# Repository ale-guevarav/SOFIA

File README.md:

# SOFIA - Sistema de Detección de Posturas

Sistema de visión por computadora desarrollado para el robot **SOFIA**, enfocado en la detección de la estructura corporal, manos y posturas de una persona en tiempo real.

El objetivo del proyecto es permitir que SOFIA pueda interpretar gestos corporales para interactuar con una persona durante una dinámica basada en el juego **Vaqueritos**.

## Primera entrega

En esta primera etapa se implementó el sistema base de visión por computadora. El programa utiliza una cámara para detectar a una persona y representar en tiempo real los puntos clave de su cuerpo y manos.

Actualmente el sistema permite:

* Capturar video en tiempo real mediante una cámara.
* Detectar la estructura corporal de una persona.
* Obtener los 33 landmarks proporcionados por MediaPipe Pose Landmarker.
* Dibujar los puntos y conexiones del esqueleto corporal.
* Filtrar landmarks corporales con baja visibilidad.
* Detectar hasta dos manos simultáneamente.
* Obtener 21 landmarks por cada mano.
* Dibujar las articulaciones y conexiones de los dedos.
* Procesar Pose y Hands simultáneamente.
* Mostrar los FPS durante la ejecución.
* Indicar visualmente si existe una persona detectada.
* Registrar métricas de desempeño (tasa de acierto, tiempo de respuesta y FPS promedio) y generar reportes en Excel y Markdown.

El sistema puede trabajar con hasta **75 landmarks simultáneamente**:

```text
33 landmarks del cuerpo
+ 21 landmarks de la mano izquierda
+ 21 landmarks de la mano derecha
= 75 landmarks
```

---

## Tecnologías utilizadas

### Python 3.12

Se eligió Python debido a su facilidad de desarrollo y a la gran cantidad de librerías disponibles para visión por computadora y procesamiento de datos.

También permite realizar prototipos rápidamente y cuenta con compatibilidad con las herramientas utilizadas en el proyecto.

### Visual Studio Code

Se utiliza Visual Studio Code como entorno de desarrollo debido a que es ligero, permite trabajar fácilmente con entornos virtuales de Python y cuenta con herramientas de depuración, terminal integrada y soporte para Git.

### OpenCV

OpenCV se utiliza principalmente para:

* Acceder a la cámara.
* Capturar los frames de video.
* Convertir formatos de imagen.
* Dibujar líneas, puntos y texto sobre la imagen.
* Mostrar el resultado del procesamiento en tiempo real.

### MediaPipe

MediaPipe proporciona los modelos de visión utilizados para obtener los landmarks del cuerpo y las manos sin necesidad de entrenar un modelo propio.

Se utilizan dos componentes:

**Pose Landmarker**

* Detecta la estructura corporal.
* Proporciona 33 landmarks.
* Permite conocer la posición de hombros, brazos, codos, muñecas, torso, piernas y otros puntos del cuerpo.

**Hand Landmarker**

* Detecta hasta dos manos.
* Proporciona 21 landmarks por mano.
* Permite obtener información de las articulaciones de los dedos.

El uso de Hand Landmarker será especialmente útil para reconocer gestos donde la posición de los dedos sea importante.

### NumPy

NumPy forma parte de las herramientas utilizadas para el procesamiento numérico y será utilizado para operaciones geométricas relacionadas con los landmarks, como cálculo de distancias, vectores y ángulos entre articulaciones.

### Matplotlib y openpyxl

Se utilizan para generar los reportes de métricas:

* **Matplotlib** crea las gráficas en imagen (pastel, barras, líneas y matriz de confusión) para el reporte en Markdown.
* **openpyxl** crea el archivo de Excel con tablas y gráficas nativas que se pueden editar.

---

## ¿Por qué se eligieron estas tecnologías?

La combinación de **Python + OpenCV + MediaPipe** permite desarrollar un sistema de visión por computadora en tiempo real sin necesidad de crear y entrenar desde cero una red neuronal para reconocimiento corporal.

Las principales ventajas para este proyecto son:

* Facilidad de implementación.
* Modelos previamente entrenados.
* Procesamiento en tiempo real.
* Detección corporal y de manos.
* Compatibilidad con cámaras convencionales.
* Gran cantidad de documentación y soporte.
* Posibilidad de calcular posturas mediante geometría a partir de los landmarks.
* Facilidad para integrar posteriormente el sistema con la lógica de SOFIA.

---

## Estructura del proyecto

```text
sofia_pose_detection/
│
├── models/
│   ├── pose_landmarker.task
│   └── hand_landmarker.task
│
├── metrics/                  (se crea automáticamente)
│   ├── sesion_*.json
│   └── reportes/
│
├── main.py
├── pose_detector.py
├── pose_connections.py
├── hand_detector.py
├── hand_connections.py
├── gesture_detector.py
├── geometry_utils.py
├── smoothing.py
├── metrics_logger.py
├── generate_report.py
├── requirements.txt
├── .gitignore
└── README.md
```

### `main.py`

Es el punto principal de ejecución del programa.

Se encarga de:

* Inicializar la cámara.
* Obtener los frames.
* Enviar las imágenes a los detectores.
* Coordinar Pose y Hands.
* Mostrar el resultado.
* Calcular los FPS.
* Registrar las métricas de desempeño.
* Liberar los recursos al finalizar.

### `pose_detector.py`

Contiene la lógica relacionada con MediaPipe Pose Landmarker.

Se encarga de detectar y dibujar la estructura corporal.

### `pose_connections.py`

Define las conexiones utilizadas para representar gráficamente el esqueleto corporal.

### `hand_detector.py`

Contiene la lógica relacionada con MediaPipe Hand Landmarker.

Se encarga de detectar y dibujar las manos y sus articulaciones.

### `hand_connections.py`

Define las conexiones entre los 21 landmarks de cada mano.

### `gesture_detector.py`

Contiene las reglas geométricas para reconocer los cinco gestos a partir de los landmarks.

### `geometry_utils.py`

Funciones de apoyo para calcular distancias, ángulos y distancias normalizadas.

### `smoothing.py`

Suavizado de landmarks (EMA) y confirmación temporal para evitar detecciones inestables.

### `metrics_logger.py`

Mide el desempeño del sistema mientras se ejecuta: FPS, latencia por frame y resultados de las pruebas. Guarda todo en un archivo JSON.

### `generate_report.py`

Lee el JSON de métricas y genera el reporte en Excel (`.xlsx`) y Markdown (`.md`) con tablas y gráficas.

### `models/`

Contiene los modelos utilizados por MediaPipe:

```text
pose_landmarker.task
hand_landmarker.task
```

---

# Posturas y gestos propuestos

Para la interacción con SOFIA se diseñaron cinco gestos inspirados en la dinámica del juego **Vaqueritos**.

En esta primera etapa los gestos se encuentran diseñados conceptualmente. Su reconocimiento automático será implementado en una etapa posterior utilizando los landmarks obtenidos por Pose Landmarker y Hand Landmarker.

## 1. INICIO - Tres palmadas

**Tipo:** Gesto dinámico.

La persona coloca las manos cerca de los muslos y realiza tres palmadas consecutivas sobre ellos.

**Función:**

Indicar el inicio de la partida o una transición hacia el modo de juego.

**Detección propuesta:**

Se analizará la distancia entre las muñecas/manos y la zona de los muslos a través de varios frames, utilizando un contador para reconocer tres movimientos consecutivos.

---

## 2. RECARGAR

**Tipo:** Postura estática.

La persona flexiona ambos brazos y coloca las manos aproximadamente a la altura de los hombros.

**Función:**

Recargar munición dentro del juego.

**Detección propuesta:**

Se utilizarán las posiciones de:

* Hombros.
* Codos.
* Muñecas.

A partir de estos landmarks será posible calcular ángulos y distancias para determinar si ambos brazos se encuentran en la posición esperada.

---

## 3. ESCUDO

**Tipo:** Postura estática.

La persona cruza los brazos frente al pecho.

**Función:**

Protegerse de un ataque.

**Detección propuesta:**

Se analizará la posición relativa de:

* Hombros.
* Codos.
* Muñecas.
* Torso.

Las muñecas deberán encontrarse cruzadas o posicionadas hacia lados opuestos del torso.

---

## 4. ATAQUE

**Tipo:** Postura principalmente estática.

La persona dirige los brazos hacia el frente y realiza con las manos un gesto similar a una pistola.

**Función:**

Realizar un ataque contra SOFIA.

**Detección propuesta:**

Pose Landmarker permitirá analizar la extensión y dirección de los brazos.

Hand Landmarker permitirá analizar individualmente los dedos para identificar una configuración similar a:

* Índice extendido.
* Pulgar extendido.
* Dedos medio, anular y meñique flexionados.

---

## 5. FIN / DESPEDIDA

**Tipo:** Gesto dinámico.

La persona levanta ambas manos y realiza un movimiento lateral de despedida.

**Función:**

Finalizar la interacción o indicar el término de la partida.

**Detección propuesta:**

Se analizará la posición de las manos durante varios frames para detectar cambios repetidos de dirección de izquierda a derecha.

---

# Flujo actual del sistema

```text
Cámara
   │
   ▼
OpenCV
   │
   ├───────────────┐
   ▼               ▼
Pose Landmarker   Hand Landmarker
   │               │
   ▼               ▼
33 landmarks      21 landmarks por mano
   │               │
   └───────┬───────┘
           ▼
Representación visual
           │
           ▼
Esqueleto + manos + FPS
```

---

# Flujo futuro

El sistema está diseñado para evolucionar hacia:

```text
Cámara
   │
   ▼
Pose + Hands
   │
   ▼
Landmarks
   │
   ▼
Detector de gestos
   │
   ├── INICIO
   ├── RECARGAR
   ├── ESCUDO
   ├── ATAQUE
   └── FIN
   │
   ▼
Lógica del juego
   │
   ▼
SOFIA
```

La lógica del juego podrá administrar aspectos como munición, acciones válidas, selección de acciones de SOFIA y condiciones de victoria o derrota.

---

# Instalación

## 1. Clonar el repositorio

```bash
git clone https://github.com/ale-guevarav/SOFIA
cd SOFIA
```

## 2. Crear un entorno virtual

```bash
python -m venv .venv
```

## 3. Activar el entorno virtual

En Windows PowerShell:

```powershell
.\.venv\Scripts\Activate.ps1
```

## 4. Instalar dependencias

```bash
pip install -r requirements.txt
```

> `requirements.txt` debe incluir `openpyxl` para poder generar el reporte en Excel.

---

# Ejecución

Con el entorno virtual activado:

```bash
python main.py
```

Se abrirá una ventana con la imagen de la cámara y la detección en tiempo real.

Para cerrar el programa:

```text
Presionar Q
```

Al cerrar se guardan automáticamente las métricas de la sesión y se genera el reporte (ver la siguiente sección).

---

# Pruebas y métricas de desempeño

El sistema incluye un modo de pruebas para medir qué tan bien funciona. Las métricas registradas son:

* **Tasa de acierto:** porcentaje de pruebas en las que el sistema reconoció el gesto correcto.
* **Tiempo de respuesta:** cuánto tarda el sistema en reconocer un gesto.
* **FPS promedio:** qué tan fluido corre el sistema.

## Controles

Las teclas solo funcionan si la **ventana de la cámara está seleccionada** (haz clic en ella antes de presionar).

| Tecla | Acción |
| --- | --- |
| `1` | Probar **INICIO** |
| `2` | Probar **RECARGAR** |
| `3` | Probar **ESCUDO** |
| `4` | Probar **ATAQUE** |
| `5` | Probar **FIN** |
| `0` / `x` | **Modo libre:** cancela la prueba actual, no registra nada y no muestra nada en pantalla |
| `s` | Guardar las métricas sin cerrar el programa |
| `q` | Salir, guardar las métricas y generar el reporte |

## ¿Cómo funciona una prueba?

Cada prueba pasa por cuatro fases:

```text
Presionar 1-5
     │
     ▼
TESTING: <gesto>  3 → 2 → 1        (naranja)
Preparación. Lo que se detecte aquí NO cuenta.
     │
     ▼
TESTING: <gesto>  YA!              (rojo parpadeando)
La persona hace el gesto. Tiene 6 segundos.
Aquí empieza a medirse el tiempo de respuesta.
     │
     ▼
ACIERTO (verde)  /  FALLO (rojo)
Se muestra 1.5 segundos.
     │
     ▼
Modo libre (pantalla limpia)
```

Mientras no se inicie una prueba, el sistema sigue midiendo FPS y latencia en segundo plano, pero no calcula la tasa de acierto, porque no sabe qué gesto se esperaba.

## ¿Cómo se califica una prueba?

El **primer gesto** que detecte el sistema después del "YA!" decide el resultado:

| Resultado | Qué significa |
| --- | --- |
| ✅ **Acierto** | El sistema detectó el gesto que se estaba probando. |
| ❌ **No detectado** | Pasaron los 6 segundos y el sistema no detectó nada. |
| ❌ **Confundido** | El sistema detectó un gesto diferente al que se estaba probando. |

Un gesto se cuenta solo en el momento en que **aparece** (cuando cambia la postura mostrada en pantalla). Si la persona mantiene un gesto por varios segundos, se cuenta como una sola detección.

## Reglas para hacer pruebas válidas

1. **Empezar en posición neutral**, con los brazos abajo. Si el gesto ya está hecho antes del "YA!", el sistema no ve un cambio y la prueba puede salir como *No detectado*.
2. **Esperar el "YA!"** antes de hacer el gesto. Lo que ocurre durante la cuenta regresiva no se toma en cuenta.
3. **Hacer un solo gesto por prueba.** Si se hace otro gesto primero, la prueba cuenta como *Confundido*.
4. **No iniciar otra prueba** mientras aparezca "TESTING". Hay que esperar a que termine o cancelarla con `0`.
5. **Mantener a la persona completa en cámara**, al menos de la cadera hacia arriba y con buena iluminación.
6. **Dividir los roles:** lo ideal es que una persona presione las teclas y otra haga los gestos.

## Protocolo recomendado

Para que los resultados sean representativos:

* Realizar **al menos 10 pruebas por gesto** (50 en total).
* Alternar el orden de los gestos en lugar de hacer todos los de un mismo tipo seguidos.
* De ser posible, repetir con **distintas personas**, distancias a la cámara y condiciones de iluminación.
* Guardar cada sesión por separado para poder compararlas.

## ¿Cómo se miden las métricas?

### Tasa de acierto

```text
Tasa de acierto = aciertos / pruebas totales × 100
```

También se calcula por cada gesto, junto con:

* **Precisión:** de las veces que el sistema dijo *X*, cuántas eran realmente *X*.
* **Recall:** de las veces que la persona hizo *X*, cuántas detectó el sistema.
* **F1:** combinación de precisión y recall en un solo valor.
* **Matriz de confusión:** tabla que muestra qué gestos se confunden entre sí. La diagonal corresponde a los aciertos.

### Tiempo de respuesta

Se mide de dos maneras:

* **Tiempo de reconocimiento (segundos):** tiempo desde el "YA!" hasta que el sistema reporta el gesto. Solo se calcula en los aciertos. Incluye el tiempo que tarda la persona en moverse y los 5 frames de confirmación temporal, por lo que representa lo que percibiría un jugador frente a SOFIA.
* **Latencia por frame (milisegundos):** cuánto tarda el programa en procesar cada imagen. Se desglosa por etapa: Pose Landmarker, Hand Landmarker, lógica de gestos y dibujo. No incluye el tiempo de espera de la cámara.

### FPS promedio

```text
FPS promedio = frames procesados / tiempo total
```

Se reportan además el FPS mínimo, máximo y p95, una gráfica de FPS a lo largo de la sesión y la **capacidad de procesamiento** (los FPS que se alcanzarían si la cámara no limitara la velocidad).

## Resultados generados

Al presionar `q` se crean los siguientes archivos:

```text
metrics/
├── sesion_AAAAMMDD_HHMMSS.json        ← datos crudos de la sesión
└── reportes/
    └── sesion_AAAAMMDD_HHMMSS/
        ├── reporte.xlsx               ← tablas y gráficas en Excel
        ├── reporte.md                 ← reporte con tablas e imágenes
        └── graficas/                  ← gráficas en PNG
```

El **Excel** contiene cinco hojas: Resumen, Por gesto, Rendimiento, Matriz de confusión e Intentos.

El **Markdown** se puede ver en VS Code con clic derecho → *Open Preview*.

Si el reporte no se generó automáticamente, o se quiere regenerar:

```bash
# Sesión más reciente
python generate_report.py

# Sesión específica
python generate_report.py metrics/sesion_AAAAMMDD_HHMMSS.json
```

---

# Estado del proyecto

### Primera etapa

* [x] Captura de cámara.
* [x] Detección corporal.
* [x] 33 landmarks corporales.
* [x] Visualización del esqueleto.
* [x] Detección de manos.
* [x] 21 landmarks por mano.
* [x] Visualización de dedos.
* [x] Procesamiento en tiempo real.
* [x] Visualización de FPS.
* [x] Modularización de detectores.
* [x] Diseño de cinco posturas/gestos.

### Segunda etapa

* [x] Suavizado de landmarks corporales (EMA).
* [x] Confirmación temporal de posturas estáticas (5 frames consecutivos).
* [x] Reconocimiento automático de ESCUDO.
* [x] Reconocimiento automático de ATAQUE (brazos + dos manos en forma de pistola).
* [x] Reconocimiento dinámico de RECARGAR.
* [x] Reconocimiento dinámico de INICIO (tres palmadas).
* [x] Reconocimiento dinámico de FIN/DESPEDIDA.
* [x] Modo de pruebas con cuenta regresiva.
* [x] Registro de métricas de desempeño (tasa de acierto, tiempo de respuesta y FPS promedio).
* [x] Generación de reportes en Excel y Markdown con tablas y gráficas.

### Próximas etapas

* [ ] Máquina de estados para evitar detecciones repetidas.
* [ ] Implementación de la lógica del juego.
* [ ] Comunicación entre el sistema de visión y SOFIA.
* [ ] Respuestas físicas del robot según las acciones del juego.

---

## Proyecto SOFIA

Proyecto académico desarrollado como sistema de interacción humano-robot mediante visión por computadora.

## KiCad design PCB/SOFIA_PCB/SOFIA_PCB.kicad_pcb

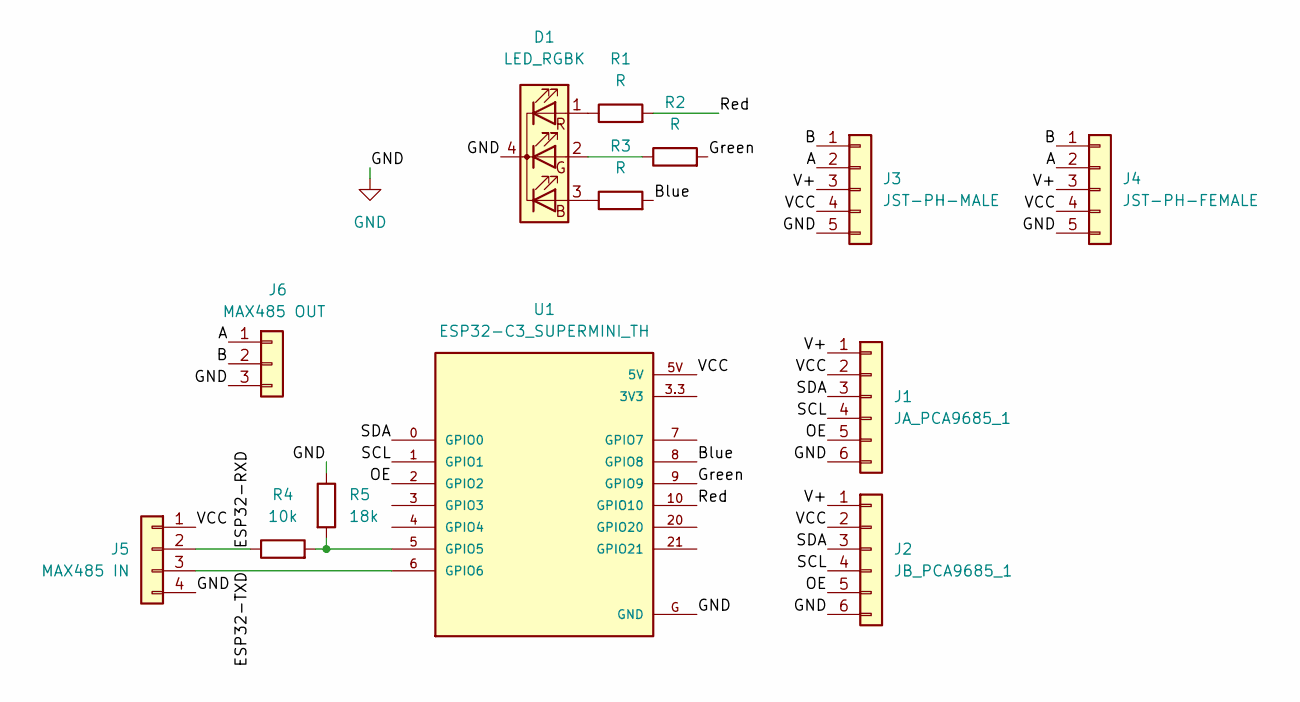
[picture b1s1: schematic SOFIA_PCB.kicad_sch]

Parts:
D1: LED_RGBK; LED_D5.0mm-4_RGB_Wide_Pins
J1: JA_PCA9685_1; PinHeader_1x06_P2.54mm_Vertical
J2: JB_PCA9685_1; PinHeader_1x06_P2.54mm_Vertical
J3: JST-PH-MALE; JST_PH_B5B-PH-K_1x05_P2.00mm_Vertical
J4: JST-PH-FEMALE; JST_PH_B5B-PH-K_1x05_P2.00mm_Vertical
J5: MAX485 IN; PinHeader_1x04_P2.54mm_Vertical
J6: MAX485 OUT; PinHeader_1x03_P2.54mm_Vertical
R1, R2, R3: R; R_Axial_DIN0207_L6.3mm_D2.5mm_P10.16mm_Horizontal
R4: 10k; R_Axial_DIN0207_L6.3mm_D2.5mm_P10.16mm_Horizontal
R5: 18k; R_Axial_DIN0207_L6.3mm_D2.5mm_P10.16mm_Horizontal
U1: ESP32-C3_SUPERMINI_TH; MODULE_ESP32-C3_SUPERMINI_TH

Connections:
/A: J3.2, J4.2, J6.1
/B: J3.1, J4.1, J6.2
/Blue: R3.2, U1.8 (GPIO8)
/ESP32-RXD: J5.2, R4.1
/ESP32-TXD: J5.3, U1.6 (GPIO6)
/Green: R2.2, U1.9 (GPIO9)
/OE: J1.5, J2.5, U1.2 (GPIO2)
/Red: R1.2, U1.10 (GPIO10)
/SCL: J1.4, J2.4, U1.1 (GPIO1)
/SDA: J1.3, J2.3, U1.0 (GPIO0)
/V+: J1.1, J2.1, J3.3, J4.3
/VCC: J1.2, J2.2, J3.4, J4.4, J5.1, U1.5V
GND: D1.4 (K), J1.6, J2.6, J3.5, J4.5, J5.4, J6.3, R5.1, U1.G (GND)
unnamed: D1.3 (BA), R3.1
unnamed: D1.2 (GA), R2.1
unnamed: D1.1 (RA), R1.1
unnamed: R4.2, R5.2, U1.5 (GPIO5)

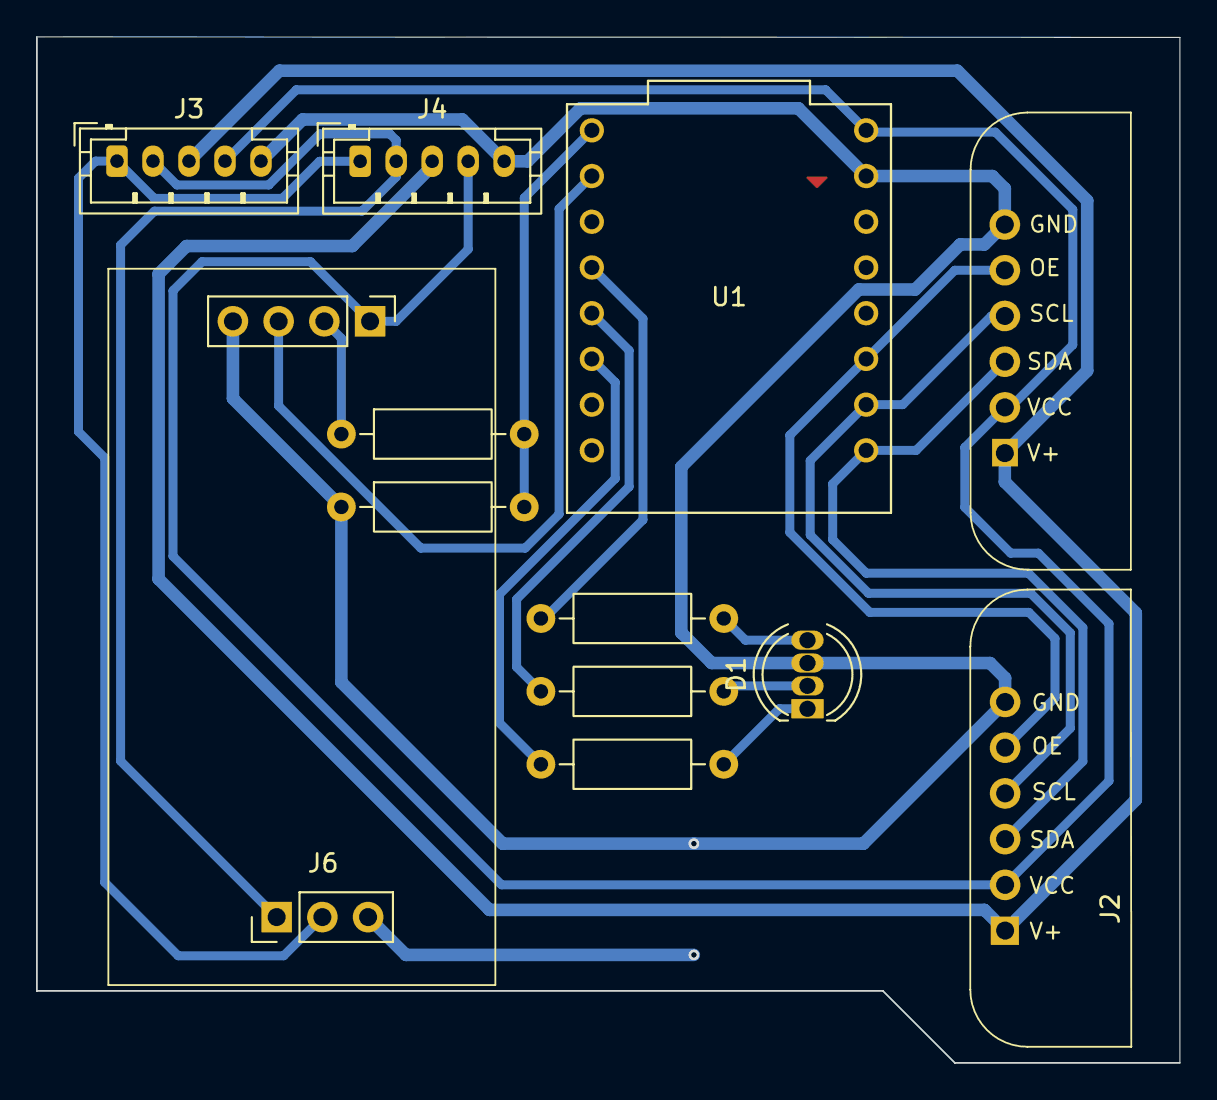
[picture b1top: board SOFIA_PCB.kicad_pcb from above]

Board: 2 copper layers, 63.5 x 57.0 mm, 13 parts (0 on the bottom side), 17 nets.

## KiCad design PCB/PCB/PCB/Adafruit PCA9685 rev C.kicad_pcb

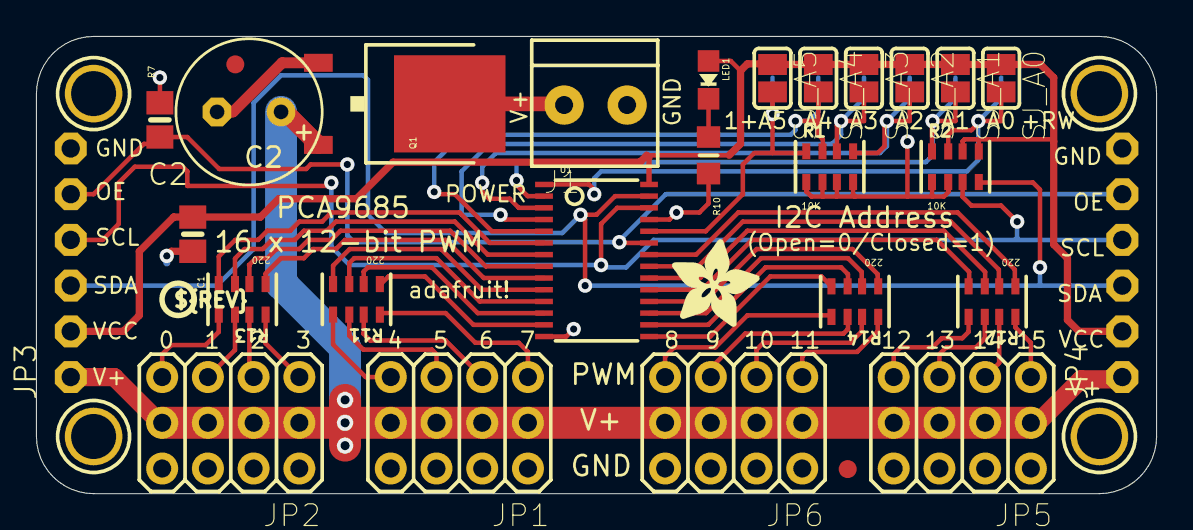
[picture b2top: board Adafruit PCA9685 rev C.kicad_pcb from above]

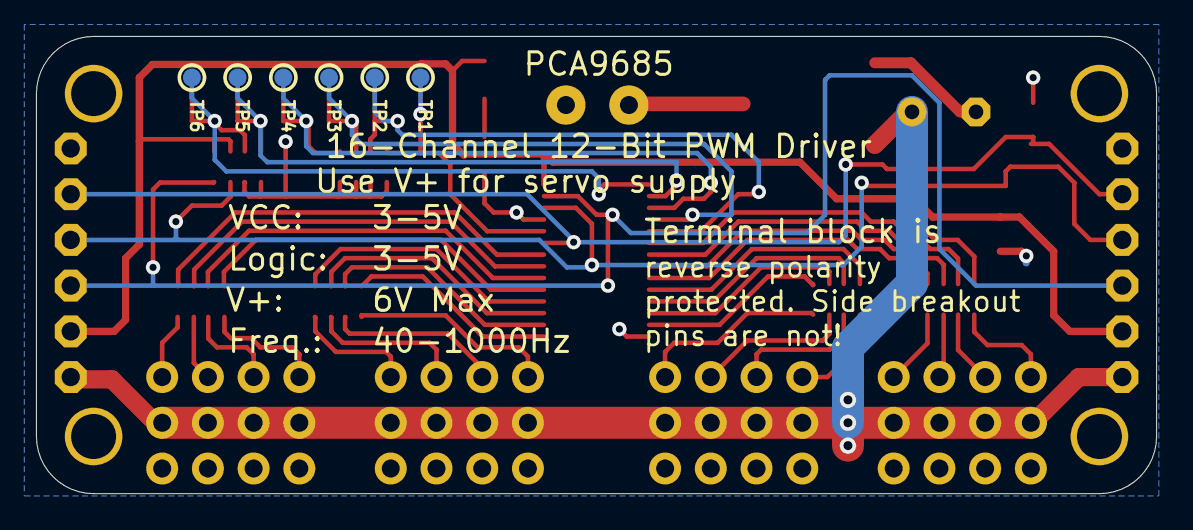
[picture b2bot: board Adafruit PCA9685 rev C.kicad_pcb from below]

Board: 2 copper layers, 62.2 x 25.4 mm, 40 parts (6 on the bottom side), 46 nets.

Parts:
C1: 10uF; 0805-NO
C2: E3,5-8
FID1, FID2: FIDUCIAL""; FIDUCIAL_1MM
J1: TERMBLOCK_1X2-3.5MM
JP1, JP2, JP5, JP6: 3X04
JP3, JP4: 1X06-CLEANBIG
LED1: GREEN; CHIPLED_0805_NOOUTLINE
Q1: AOD417; TO252
R1, R2: 10K; RESPACK_4X0603
R7: 10K; 0805-NO
R10: 470; _0805MP
R11, R12, R13, R14: 220; RESPACK_4X0603
SJ_A0, SJ_A1, SJ_A2, SJ_A3, SJ_A4, SJ_A5: SOLDERJUMPER_REFLOW_NOPASTE
TP1, TP2, TP3, TP4, TP5, TP6: TESTPOINT_ROUND_1MM
U1: PCA9685; TSSOP28
U$47, U$48, U$49, U$50: MOUNTINGHOLE2.5; MOUNTINGHOLE_2.5_PLATED
U$51: ADAFRUIT_5MM
U$54: PCBFEAT-REV-040

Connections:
5.0V: C2.+, JP1.2, JP1.5, JP1.8, JP1.11, JP2.2, JP2.5, JP2.8, JP2.11, JP3.1, JP4.1, JP5.2, JP5.5, JP5.8, JP5.11, JP6.2, JP6.5, JP6.8, JP6.11, Q1.2
A0: R2.7, SJ_A0.2, TP6.P$1, U1.1
A1: R2.8, SJ_A1.2, TP5.P$1, U1.2
A2: R1.5, SJ_A2.2, TP4.P$1, U1.3
A3: R1.6, SJ_A3.2, TP3.P$1, U1.4
A4: R1.7, SJ_A4.2, TP2.P$1, U1.5
A5: R1.8, SJ_A5.2, TP1.P$1, U1.24
GND: C1.2, C2.-, J1.2, JP1.3, JP1.6, JP1.9, JP1.12, JP2.3, JP2.6, JP2.9, JP2.12, JP3.6, JP4.6, JP5.3, JP5.6, JP5.9, JP5.12, JP6.3, JP6.6, JP6.9, JP6.12, Q1.1, R1.1, R1.2, R1.3, R1.4, R2.1, R2.2, R7.2, R10.2, U1.14, U1.25
unnamed: LED1.C, R10.1
unnamed: JP1.4, R11.7
unnamed: JP1.1, R11.8
unnamed: JP1.7, R11.6
unnamed: JP1.10, R11.5
unnamed: JP2.1, R13.8
unnamed: JP2.4, R13.7
unnamed: JP2.7, R13.6
unnamed: JP2.10, R13.5
unnamed: JP6.10, R14.5
unnamed: JP6.7, R14.6
unnamed: JP6.4, R14.7
unnamed: JP6.1, R14.8
unnamed: JP5.10, R12.5
unnamed: JP5.7, R12.6
unnamed: JP5.4, R12.7
unnamed: JP5.1, R12.8
OE: JP3.5, JP4.5, R7.1, U1.23
PWM0: R13.4, U1.6
PWM1: R13.3, U1.7
PWM2: R13.2, U1.8
PWM3: R13.1, U1.9
PWM4: R11.4, U1.10
PWM5: R11.3, U1.11
PWM6: R11.2, U1.12
PWM7: R11.1, U1.13
PWM8: R14.4, U1.15
PWM9: R14.3, U1.16
PWM10: R14.2, U1.17
PWM11: R14.1, U1.18
PWM12: R12.4, U1.19
PWM13: R12.3, U1.20
PWM14: R12.2, U1.21
PWM15: R12.1, U1.22
PWRIN: J1.1, Q1.3
SCL: JP3.4, JP4.4, R2.3, U1.26
SDA: JP3.3, JP4.3, R2.4, U1.27
VCC: C1.1, JP3.2, JP4.2, LED1.A, R2.5, R2.6, SJ_A0.1, SJ_A1.1, SJ_A2.1, SJ_A3.1, SJ_A4.1, SJ_A5.1, U1.28
